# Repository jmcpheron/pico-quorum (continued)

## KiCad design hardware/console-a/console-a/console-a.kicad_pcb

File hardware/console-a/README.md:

# The console PCB, rev A ("console-a")

> **Status: designed and checked, not ordered.** ERC 0, DRC 0, nothing unconnected, schematic
> parity clean (`tools/keypcb check console-a/console-a`, 2026-10-07, KiCad 10.0.6). No board has been made
> and nothing on it has been tried on a bench. Before ordering, see
> [what to check first](#check-these-before-ordering).

Not to be confused with [`console-pcb/console-a`](../console-pcb/README.md), the one-board Build 1
(2.8″ screen, knob, USB-C plug), drawn in parallel. Both are called console-a, so `tools/keypcb`
names this one `console-a/console-a`.

One board that holds the whole console: a Pico 2 W, a bare 1.3″ 240×240 color panel, nine buttons,
and pads for the key. It's wired exactly like the Waveshare Pico-LCD-1.3, so **the console image
runs on it unchanged**. It keeps `BOARD = "waveshare"` (the default), with no firmware change and
no new release.

| front | back |
|---|---|
|  |  |

These are KiCad renders, without the panel. The front shows the panel's connector where the panel
will sit. On the back, the Pico 2 W is soldered flat, chips facing out.

| | |
|---|---|
| Board | 92 × 52 mm, 2 layers, 1.6 mm, lead-free HASL, a notch in the top edge under the Pico's antenna, 4 × M2.5 holes |
| JLCPCB places | on the front: 9 buttons, the panel connector, the key-port parts, the backlight switch (30 parts, 3 of them Extended). On the back, if you ask: the Pico 2 W |
| You plug in | the panel's flex, into J2 (no solder) |
| You solder | the key's wires to J3, and the Pico if JLCPCB doesn't |
| Files | `console-a/` (KiCad 10), fab files in `console-a/fab/`, made by [`gen.py`](gen.py) |

How to order it: [ORDERING.md](ORDERING.md).

## Two ways to build it

It's the same board and the same Gerbers either way. Only the BOM and CPL you upload differ.

| | Pico soldered by you | Pico soldered by JLCPCB |
|---|---|---|
| Files | `fab/bom.csv`, `fab/cpl.csv` | `fab/factory-pico/bom.csv`, `fab/factory-pico/cpl.csv` |
| JLCPCB fits | the 30 front parts | the same 30, plus U1, the Pico 2 W, on the back |
| Assembly | one side | both sides, with X-ray (JLCPCB requires it for this part) |
| The Pico | you buy one without headers (about $7) and solder 40 pads by hand | LCSC **C42394205**, Raspberry Pi SC1633 (the Pico 2 W without headers), $11.68 on 2026-10-07 |
| You still do | the panel, the key's wires | the panel, the key's wires |

The factory route costs more per board (the dearer Pico, a second side, X-ray), but nobody holds an
iron to 40 pads per console. JLCPCB had 82 in stock on 2026-10-07. For more, pre-order them into
your JLCPCB parts library before the order. Parts there can only be used in assembly, not shipped
to you. Only JLCPCB's quote shows the real price, and its preview shows how they'll place a module
on the back. Check both before paying (ORDERING.md).

## The pin map

This is the Waveshare board's map, and `firmware/board.py`'s. `gen.py` has it as one table,
`PINS`. `python3 hardware/console-a/gen.py check` (or `tools/keypcb check console-a/console-a`) checks it
three ways: against `firmware/board.py`, against the emulator's `emu/core/runtime.mjs`, and against
the nets on the saved board.

| signal | GPIO | | signal | GPIO |
|---|---|---|---|---|
| LCD DC | GP8 | | A (Sign) | GP15 |
| LCD CS | GP9 | | B (Back) | GP17 |
| LCD SCK | GP10 | | X (Device) | GP19 |
| LCD MOSI | GP11 | | Y (Reject) | GP21 |
| LCD RST | GP12 | | up | GP2 |
| LCD backlight | GP13 | | down | GP18 |
| key SDA | GP4 | | left | GP16 |
| key SCL | GP5 | | right | GP20 |
| key power enable | GP6 | | press (centre) | GP3 |
| key DETECT (spare pad) | GP7 | | key CC1 | GP27 (ADC1) |
| spare pad | GP26 | | key CC2 | GP28 (ADC2) |

The buttons pull their GPIO to ground. The firmware's internal pull-ups do the rest, so there are no
resistors. The d-pad is five buttons: four directions and a centre press. A, B, X and Y sit in a
column to the right of the screen, top to bottom, the way the emulator draws them.

## The panel

**ZJY130T-IF05** (its drawing says ZJY133T-IF05): 1.3″ IPS, 240×240, ST7789VW driver, 4-wire SPI,
two white backlight LEDs. It has a 24-pin, 0.5 mm flex tail that folds behind the panel. It's from
the same ZJY 1.3″ family as the Waveshare board's panel. The Waveshare schematic's 12 panel pins
match ZJY133T-IG01, the solder-tail sibling.
- Datasheet: the ZJY133T-IF05 spec, published by both sellers in
  [Getting the right panel](#getting-the-right-panel). LCSC doesn't stock this panel.
- Wiring, as on the Waveshare board:
  - The backlight is switched on its low side by Q1 (SS8050) from GP13, with a 10 Ω resistor in
    series. That's about 30 mA.
  - IM1/2 and RD are tied high, which selects SPI. DB0–DB7 are tied to ground. TE isn't used.
- **Pin 9 is the SPI clock, and pin 10 is D/C.** The datasheet's pin table calls them "D/C" and
  "WR", but its descriptions say so, and that's how the ST7789 works in 4-wire mode.
- **Contact k on J2 is panel pin 25 − k.** J2 sits turned so the flex goes in from the right, which
  puts J2's own pin 1 at the bottom. The panel's pin 1 is at the top. The schematic does the
  swap, so the nets are right on the copper.
- **Why the flex goes to the right.** The firmware sets MADCTL 0x70 (row/column exchange and X
  mirror, no RAM offset). From the native portrait view, with the flex at the bottom, that turns the
  picture a quarter turn so the flex ends up on the picture's right side. Waveshare's photos agree:
  their wider bezel is on the button side. If the picture comes out rotated anyway, nothing on the
  board needs to change except the panel's way round. See the checklist below.
- J2 is a Jushuo **AFC07-S24FCA-00** (LCSC C262567): a bottom-contact, slide-lock 0.5 mm connector,
  2 mm tall. It sits under the panel, 12.8 mm in from the panel's right edge. That's where the folded
  tail ends on the drawing.
- The panel rests on 2–2.5 mm foam tape, over J2 and the small parts under it.

## Getting the right panel

Many 1.3″ screens look alike, and most of them won't fit J2. The right one is all of these:
- **ZJY133T-IF05** (also sold as ZJY130T-IF05)
- 1.3″ IPS, 240×240, ST7789V or ST7789VW driver
- a **24-pin plug-in flex at 0.5 mm pitch**, 12.5 mm wide, made to fold behind the panel

**Where to buy it.** These two sellers publish the ZJY133T-IF05 datasheet. Their pin tables are
identical to the one this board was designed to (compared on 2026-10-07):

| seller | listing | price on 2026-10-07 |
|---|---|---|
| Adafruit | [4520](https://www.adafruit.com/product/4520), "1.3 240x240 Wide Angle TFT LCD Display, bare" | $12.50, $11.25 at 10+, $10 at 100+ |
| Smart Prototyping | [102108](https://www.smart-prototyping.com/1_3-inch-TFT-IPS-Bare-Display-ST7789-SPI-240-240): **pick "Plug-in type 24pin"**, not the default 12-pin welded type | $8.90, $8 at 30+, $7.50 at 100+ |

Adafruit's page says the panel wants a bottom-contact connector, and J2 is one.

**Another seller, or a cheaper one.** Ask for the datasheet before buying, and check that its pin
table matches this one line for line. No datasheet, no order.

| pin | name | pin | name | pin | name |
|---|---|---|---|---|---|
| 1 | LEDA | 9 | D/C (the SPI clock) | 17 | DB4 |
| 2 | LEDK | 10 | WR (D/C in SPI) | 18 | DB5 |
| 3 | GND | 11 | RD | 19 | DB6 |
| 4 | VDD | 12 | SDA | 20 | DB7 |
| 5 | IOVCC | 13 | DB0 | 21 | TE |
| 6 | IM1/2 | 14 | DB1 | 22 | NC |
| 7 | RESET | 15 | DB2 | 23 | GND |
| 8 | CS | 16 | DB3 | 24 | GND |

**Look-alikes that won't work:**
- the same panel with the **12-pin solder tail** (the one on the Waveshare board)
- red or blue breakout boards with a 7- or 8-pin header
- round 1.28″ GC9A01 panels
- 1.3″ ST7735 panels
- 1.54″ and 1.69″ panels, and 240×280 panels
- anything whose tail isn't 24 contacts at 0.5 mm

**Check each batch when it arrives:**
1. Count 24 contacts, and measure the tail's end: 12.5 mm wide.
2. Fold the tail behind the panel the way it will sit, and look at the contacts. They should face
   away from the panel, toward the board.
3. First article: plug one into an assembled board and flash the console image. The picture should
   be upright with the flex on its right, and the backlight should light. Then fit the rest.

**Getting panels into each console.** JLCPCB can't fit or ship the panels, so they come to you:
- Buy them yourself, with about 10% spare: tails tear.
- Fitting one takes about a minute and no solder:
  1. Slide J2's latch out.
  2. Push the tail in straight, contacts down.
  3. Slide the latch back.
  4. Fold the panel over onto 2–2.5 mm foam tape.
- For consoles you hand out, fit and test each panel before it leaves (step 3 above for every
  unit). Or ship the panel loose with the four steps on a card, if the people building them are
  comfortable with a 0.5 mm latch.

## The key port

J3 is a row of eight 2.54 mm through-hole pads on the right edge, for wires to a USB-C receptacle or
straight to a key. From the top:

| J3 | net | key-c |
|---|---|---|
| 1 | GND | GND |
| 2 | KEY_VBUS | VBUS |
| 3 | SDA | D+ |
| 4 | SCL | D− |
| 5 | CC1 | CC1 |
| 6 | CC2 | CC2 |
| 7 | GP7 (DETECT) | spare |
| 8 | GP26 | spare |

Behind the pads is the circuit that [PROPOSALS.md](../key-pcb/PROPOSALS.md#the-console-end-of-key-c)
asks for before the port is more than a bench socket:

- **U2, TPS22945:** a load switch from 3V3, with a 100 mA current limit, enabled by GP6 (pulled
  down by R4). A phone or a shorted cable gets 100 mA, not the Pico's whole supply.
- **D1, B5819W Schottky:** sits between U2 and VBUS, so a charger's 5 V can't reach U2's output,
  the pull-ups, or 3V3. The TPS22945 doesn't block reverse current itself (datasheet 9.1.3). The
  diode does, and the key gets about 3.0 V, inside the ATECC608's 2.0–5.5 V.
- **R7, R8:** 2.2 kΩ pull-ups on SDA and SCL, to the switched supply (KEY_PWR), never to 3V3. A
  key with its power off isn't fed through its I2C pins.
- **R5, R6:** bleed KEY_PWR and VBUS down, so a key really loses power when U2 turns off.
- **CC1 and CC2 are read separately,** on GP27 and GP28, each through its own 10 kΩ Rp to 3V3:
  - A key's 5.1 kΩ Rd reads about 1.1 V.
  - An e-marked cable's Ra (about 1 kΩ) reads about 0.3 V.
  - Nothing connected reads 3.3 V.
  - A key shows exactly one Rd.
  - A charger's Rp (56 kΩ to 5 V) can lift a CC pin to about 3.6 V. That's inside the RP2350's
    rating, and the current is tens of µA.
- **U3, U4, USBLC6-2SC6:** ESD arrays on SDA/SCL and CC1/CC2, as on the key.

**Today's console image doesn't switch GP6.** Only `firmware/bench1.py` does, so a key on J3 gets
no power from the console as shipped. Two ways to use it:

1. Close **JP1 "KEY ON"** with a blob of solder. R11 (10 kΩ) then holds U2 on whenever the console
   is on. You keep the current limit and the 5 V block, but not the power cut when a key comes out.
   Because it goes through R11, firmware that drives GP6 low later still wins.
2. Run firmware that does what `bench1.py` does: wait for the key, switch GP6, scan. Reading CC
   needs new firmware too. Both are firmware changes, so a new release
   (`docs/RELEASES.md`), and not part of this board.

## Check these before ordering

These come from datasheets and photos, not from a board on the bench.

- [ ] **Buy one panel first** and look at its tail:
  - Is it 24 pins at 0.5 mm, with the pin table above?
  - Which face are the contacts on, once the tail is folded behind the panel?
  - J2 as ordered is bottom-contact (contacts toward the PCB), which is what Adafruit says this
    panel wants. If the folded tail's contacts face up anyway, order **AFC07-S24ECA-00 (C262643)**
    instead: same footprint, other contact side.
- [ ] Check the folded tail's length: its end should reach about 12.8 mm in from the panel's
  edge, at J2's latch.
- [ ] Check the orientation on a Waveshare board you already have: the flex should come out on
  the right side of the picture. If not, turn the panel's outline on the board (and J2 with it)
  before ordering.
- [ ] Check every part's rotation and pin 1 in JLCPCB's placement preview, especially J2, U2, U3,
  U4, Q1 and D1 (on key-c, a SOIC-8 and a SOT-23-6 came up 90° off).
- [ ] Hold a Pico 2 W on the back:
  - Its antenna end sits over the notch.
  - Its USB plug clears the bottom edge.
  - The two USB-connector pegs drop into their holes.

## How it's made

[`gen.py`](gen.py) writes the whole KiCad project from scratch. `tools/keypcb gen-console-a` runs it
with KiCad's Python. It reuses the key boards' helpers (`../key-pcb/gen.py`):
- **The schematic** is drawn from one parts table. Every pin gets a short wire and its net's
  label, so the drawing is plain, not pretty.
- **[`router.py`](router.py) lays the tracks.** It's a small two-layer router: A* on a 0.25 mm
  grid, 0.25 mm tracks, 0.15 mm clearance, 0.6/0.3 mm vias. It's pure Python.
  - A few things are placed by hand first, with the reasons in `gen.py`: the ground stubs under
    J2's body, J2's RD contact, U2's ground pin, and the runs of same-net contacts on J2.
  - Every front ground pad gets a via to the back pour.
  - KiCad's DRC then checks all of it again.
- **The Pico's footprint** is KiCad's `RaspberryPi_Pico_W_SMD_HandSolder` with two changes,
  written to `lib/console.pretty`:
  - Its three SWD through-holes are gone: they would land under J2. Flashing is over USB.
  - Its "RF Copper Keep Out" is gone, because DRC flags the module's own end pads against it. A
    pour-free strip along the top edge keeps its intent.

As with the key boards, once you edit the board in KiCad, the KiCad files are the source of truth:
don't run `gen.py` again, or your edits are lost. The routing is DRC-clean, not hand-polished.
Around J2 it's dense, and you may want to tidy it in the GUI.

**Not on this board, on purpose:** a battery, a USB-C receptacle for the key (J3 takes wires), a
rotary knob, SWD pads, and an enclosure.

## Log

- **2026-10-08:**
  - **Factory-soldered Pico** added as a second assembly option (`fab/factory-pico/`). The board,
    the Gerbers and the default BOM and CPL are unchanged.
  - U1's part number corrected to SC1633, the Pico 2 W without headers (SC1634 is the version
    with headers).
  - "Getting the right panel" added: Adafruit 4520 confirmed as the same ZJY133T-IF05.

- **2026-10-07:** rev A designed: the parts chosen, routed, checked (ERC 0, DRC 0, parity clean,
  pin map matched three ways), and the fab files written. Not ordered.

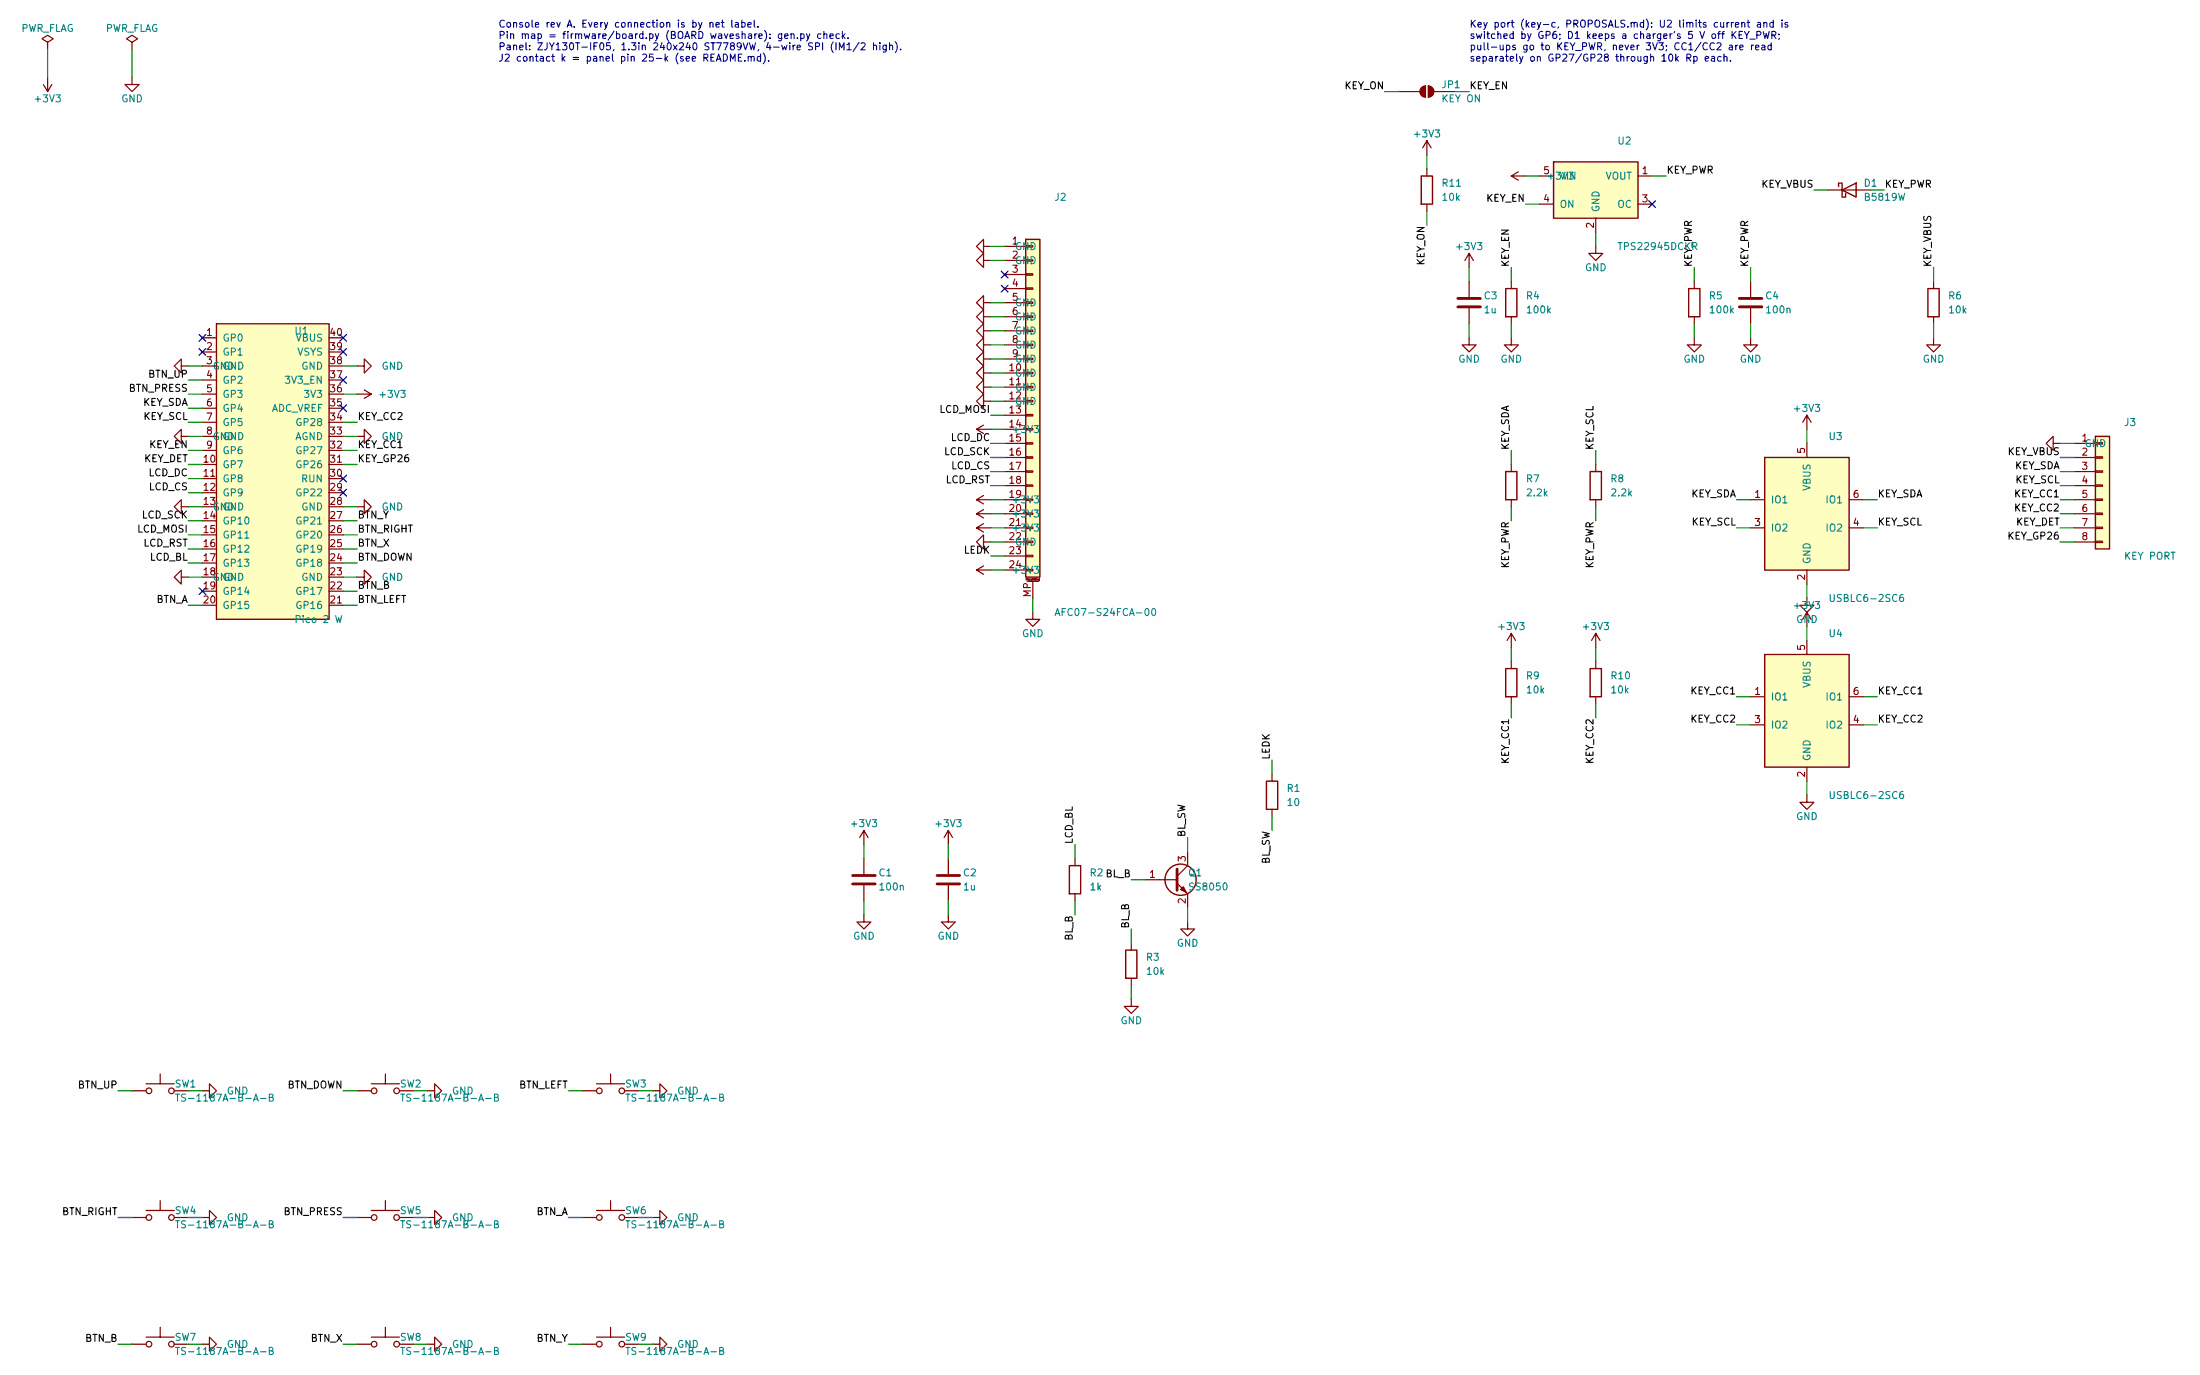
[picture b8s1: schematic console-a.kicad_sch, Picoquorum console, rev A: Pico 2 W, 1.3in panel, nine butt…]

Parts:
C1, C4: 100n; C_0603_1608Metric; LCSC C14663
C2, C3: 1u; C_0603_1608Metric; LCSC C15849
D1: B5819W; D_SOD-123; MPN B5819W SL; LCSC C8598
J2: AFC07-S24FCA-00; Jushuo_AFC07-S24FCA-00_1x24-1MP_P0.50_Horizontal; MPN AFC07-S24FCA-00; LCSC C262567
J3: KEY PORT; PinHeader_1x08_P2.54mm_Vertical
JP1: KEY ON; SolderJumper-2_P1.3mm_Open_RoundedPad1.0x1.5mm
Q1: SS8050; SOT-23; MPN SS8050; LCSC C2150
R1: 10; R_0603_1608Metric; LCSC C22859
R2: 1k; R_0603_1608Metric; LCSC C21190
R3, R6, R9, R10, R11: 10k; R_0603_1608Metric; LCSC C25804
R4, R5: 100k; R_0603_1608Metric; LCSC C25803
R7, R8: 2.2k; R_0603_1608Metric; LCSC C4190
SW1, SW2, SW3, SW4, SW5, SW6, SW7, SW8, SW9: TS-1187A-B-A-B; SW_Push_1P1T_XKB_TS-1187A; LCSC C318884
U1: Pico 2 W; RaspberryPi_Pico_W_SMD_HandSolder_PQ; MPN SC1633; LCSC_FACTORY C42394205
U2: TPS22945DCKR; SOT-353_SC-70-5; MPN TPS22945DCKR; LCSC C47507
U3, U4: USBLC6-2SC6; SOT-23-6; MPN USBLC6-2SC6; LCSC C7519

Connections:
+3V3: C1.1, C2.1, C3.1, J2.14, J2.19, J2.20, J2.21, J2.24, R9.1, R10.1, R11.1, U1.36 (3V3), U2.5 (VIN), U3.5 (VBUS), U4.5 (VBUS)
/BL_B: Q1.1 (B), R2.2, R3.1
/BL_SW: Q1.3 (C), R1.2
/BTN_A: SW6.1, U1.20 (GP15)
/BTN_B: SW7.1, U1.22 (GP17)
/BTN_DOWN: SW2.1, U1.24 (GP18)
/BTN_LEFT: SW3.1, U1.21 (GP16)
/BTN_PRESS: SW5.1, U1.5 (GP3)
/BTN_RIGHT: SW4.1, U1.26 (GP20)
/BTN_UP: SW1.1, U1.4 (GP2)
/BTN_X: SW8.1, U1.25 (GP19)
/BTN_Y: SW9.1, U1.27 (GP21)
/KEY_CC1: J3.5, R9.2, U1.32 (GP27), U4.1 (IO1), U4.6 (IO1)
/KEY_CC2: J3.6, R10.2, U1.34 (GP28), U4.3 (IO2), U4.4 (IO2)
/KEY_DET: J3.7, U1.10 (GP7)
/KEY_EN: JP1.2 (B), R4.1, U1.9 (GP6), U2.4 (ON)
/KEY_GP26: J3.8, U1.31 (GP26)
/KEY_ON: JP1.1 (A), R11.2
/KEY_PWR: C4.1, D1.2 (A), R5.1, R7.2, R8.2, U2.1 (VOUT)
/KEY_SCL: J3.4, R8.1, U1.7 (GP5), U3.3 (IO2), U3.4 (IO2)
/KEY_SDA: J3.3, R7.1, U1.6 (GP4), U3.1 (IO1), U3.6 (IO1)
/KEY_VBUS: D1.1 (K), J3.2, R6.1
/LCD_BL: R2.1, U1.17 (GP13)
/LCD_CS: J2.17, U1.12 (GP9)
/LCD_DC: J2.15, U1.11 (GP8)
/LCD_MOSI: J2.13, U1.15 (GP11)
/LCD_RST: J2.18, U1.16 (GP12)
/LCD_SCK: J2.16, U1.14 (GP10)
/LEDK: J2.23, R1.1
GND: C1.2, C2.2, C3.2, C4.2, J2.1, J2.2, J2.5, J2.6, J2.7, J2.8, J2.9, J2.10, J2.11, J2.12, J2.22, J2.MP (MountPin), J3.1, Q1.2 (E), R3.2, R4.2, R5.2, R6.2, SW1.2, SW2.2, SW3.2, SW4.2, SW5.2, SW6.2, SW7.2, SW8.2, SW9.2, U1.3 (GND), U1.8 (GND), U1.13 (GND), U1.18 (GND), U1.23 (GND), U1.28 (GND), U1.33 (AGND), U1.38 (GND), U2.2 (GND), U3.2 (GND), U4.2 (GND)

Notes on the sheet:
Console rev A. Every connection is by net label. Pin map = firmware/board.py (BOARD waveshare): gen.py check. Panel: ZJY130T-IF05, 1.3in 240x240 ST7789VW, 4-wire SPI (IM1/2 high). J2 contact k = panel pin 25-k (see README.md).
Key port (key-c, PROPOSALS.md): U2 limits current and is switched by GP6; D1 keeps a charger's 5 V off KEY_PWR; pull-ups go to KEY_PWR, never 3V3; CC1/CC2 are read separately on GP27/GP28 through 10k Rp each.

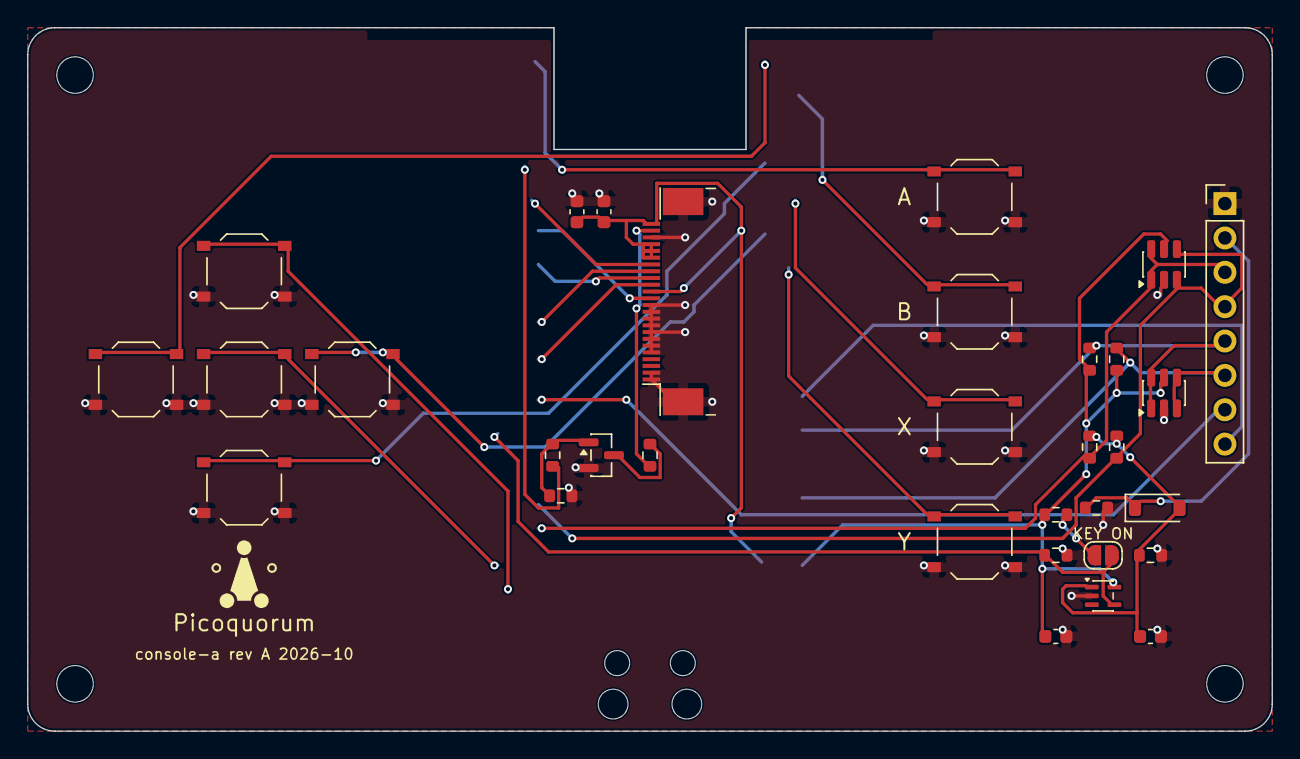
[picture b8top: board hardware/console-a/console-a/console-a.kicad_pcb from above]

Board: 2 copper layers, 92.0 x 52.0 mm, 38 parts (1 on the bottom side), 30 nets.

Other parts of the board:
H1, H2, H3, H4: M2.5; MountingHole_2.7mm_M2.5
LOGO1: PicoQuorum_Mark

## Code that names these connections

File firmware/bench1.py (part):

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SCR_MOSI = 11
SCR_RST = 12
SCR_BL = 13
ENC_A = 2
ENC_B = 3
ENC_SW = 1
KEY_SDA = 4
KEY_SCL = 5
KEY_PWR = 6
KEY_DETECT = 7
KEY_RST = 26            # J2 ring 1; left alone here (a Trust M key soft-resets over I2C)
KEY_ID = 27             # J2 ring 2; open on every Build 1 key
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

# --- knob: quadrature on two edge interrupts; on an ESP32, its pulse counter (knob.py says why) ---
_enc_a = Pin(ENC_A, Pin.IN, Pin.PULL_UP)
_enc_b = Pin(ENC_B, Pin.IN, Pin.PULL_UP)
_push = Pin(ENC_SW, Pin.IN, Pin.PULL_UP)
_QUAD = (0, -1, 1, 0, 1, 0, 0, -1, -1, 0, 0, 1, 0, 1, -1, 0)
_enc_state = (_enc_a.value() << 1) | _enc_b.value()
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    from machine import Encoder
    _enc = Encoder(0, _enc_a, _enc_b, phases=4, filter_ns=10_000)
else:
    _enc_a.irq(_enc_irq, Pin.IRQ_RISING | Pin.IRQ_FALLING, hard=True)    # knob.py says why hard
    _enc_b.irq(_enc_irq, Pin.IRQ_RISING | Pin.IRQ_FALLING, hard=True)


def count():
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if JACKS:
    _detect = Pin(KEY_DETECT, Pin.IN, Pin.PULL_UP)
    try:
        _pwr = Pin(KEY_PWR, Pin.OUT, value=0, drive=Pin.DRIVE_3)   # 12 mA drive where the port has it
    except (AttributeError, TypeError, ValueError):
        _pwr = Pin(KEY_PWR, Pin.OUT, value=0)


def release_bus():
    """SDA and SCL back to plain inputs, no pull-ups, so nothing feeds an unpowered chip through them."""
    Pin(KEY_SDA, Pin.IN, pull=None)
    Pin(KEY_SCL, Pin.IN, pull=None)


def power(on):
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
